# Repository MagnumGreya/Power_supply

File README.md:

# Power_supply
A SIMPLE PCB DESIGN FOR A 12V INPUT,(3.3V 5V 1A)DC POWER OUTPUT MODULE

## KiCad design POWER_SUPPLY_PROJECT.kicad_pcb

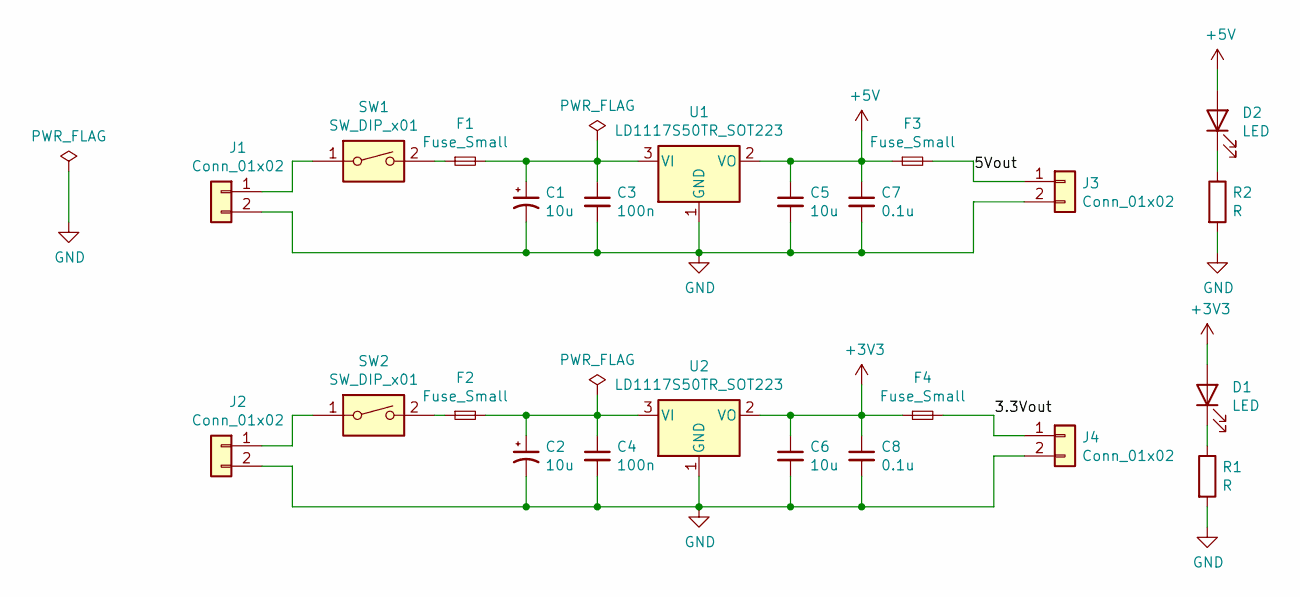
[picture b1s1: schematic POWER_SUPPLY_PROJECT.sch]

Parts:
C1: 10u; CP_Elec_3x5.4
C2, C5, C6: 10u; C_1206_3216Metric
C3, C4: 100n; C_1206_3216Metric
C7, C8: 0.1u; C_1206_3216Metric
D1, D2: LED; LED_D3.0mm
F1, F2, F3, F4: Fuse_Small; Fuse_1206_3216Metric
J1, J2, J3, J4: Conn_01x02; TerminalBlock_Phoenix_MKDS-1,5-2_1x02_P5.00mm_Horizontal
R1: R; R_Axial_DIN0207_L6.3mm_D2.5mm_P7.62mm_Horizontal
R2: R; R_1206_3216Metric
SW1: SW_DIP_x01; SW_DIP_SPSTx01_Slide_6.7x4.1mm_W8.61mm_P2.54mm_LowProfile
SW2: SW_DIP_x01; SW_DIP_SPSTx01_Slide_6.7x4.1mm_W6.73mm_P2.54mm_LowProfile_J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
U1, U2: LD1117S50TR_SOT223; SOT-223-3_TabPin2

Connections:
+3V3: C6.1, C8.1, D1.2 (A), F4.1, U2.2 (VO)
+5V: C5.1, C7.1, D2.2 (A), F3.1, U1.2 (VO)
/3.3Vout: F4.2, J4.1
/5Vout: F3.2, J3.1
GND: C1.2, C2.2, C3.2, C4.2, C5.2, C6.2, C7.2, C8.2, J1.2, J2.2, J3.2, J4.2, R1.2, R2.2, U1.1 (GND), U2.1 (GND)
unnamed: C1.1, C3.1, F1.2, U1.3 (VI)
unnamed: C2.1, C4.1, F2.2, U2.3 (VI)
unnamed: D1.1 (K), R1.1
unnamed: D2.1 (K), R2.1
unnamed: F1.1, SW1.2
unnamed: F2.1, SW2.2
unnamed: J1.1, SW1.1
unnamed: J2.1, SW2.1

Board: 2 copper layers, 24 parts (0 on the bottom side), 13 nets, no tracks yet.

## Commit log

2021-07-25 Schema and footprints
